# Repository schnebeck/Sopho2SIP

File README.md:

# ErgoLine D340 – Protokoll der PC-Schnittstelle

Offene Dokumentation des seriellen Protokolls, mit dem ein PC ein Philips-Systemtelefon **ErgoLine D340**
(Anlage **Sopho iS3000**, Telekom-Variante Octophon 340) steuert: Anrufe erkennen – mit Anrufernummer –,
annehmen, wählen und auslösen. Ziel: Jede und jeder soll damit einen eigenen TAPI- oder SIP-Daemon bauen können.

**➜ Spezifikation lesen: [schnebeck.github.io/Sopho2SIP/protokoll.html](https://schnebeck.github.io/Sopho2SIP/protokoll.html)**
(im Repository: [`docs/protokoll.html`](docs/protokoll.html))

Die Spezifikation enthält Rahmenformat, alle Meldungen und Aufträge, Zeitverhalten, Ablauf- und Zustandsdiagramme,
die Zuordnung zu SIP und einen Leitfaden für den Daemon. Jede Angabe ist gekennzeichnet als
**bestätigt** (am Gerät gemessen), **Treiber** (aus dem Philips-Treiber abgeleitet) oder **vermutet**.

## Kurzfassung

| | |
|---|---|
| Anschluss | 9-polige Buchse hinten am Telefon, 1:1-Kabel, Pin 2/3/5 |
| Freischaltung | am Telefon: Merkmale → Optionen → „TAPI: Sprache über Telefon“ = Ein |
| Leitung | 1200 Baud, 8O1 |
| Rahmen | `Klasse · Länge · Nutzdaten` – ohne Prüfsumme, ohne Start-/Endzeichen |
| Klassen | `01` Auftrag PC · `02` Meldung Telefon · `03` REJ · `04` ACK · `05` ERR |
| Meldungen | `30` RINGING (mit Anrufernummer) · `31` CONNECTED · `32` DISCONNECTED · `36` DIALTONE · `39` RELEASED · `3e` PROCEEDING · … |
| Aufträge | Anmelden `01 02 01 00` · Wählen `01 L 19 00 98 70 …` · Annehmen `01 02 14 00` · Auflegen `01 02 13 00` |

## Stand

- Empfangsrichtung vollständig mitgeschnitten und entschlüsselt (Anruf mit Nummer, Wahl, Verbindung, Auslösung).
- Senderichtung aus dem originalen Philips-Treiber abgeleitet; der erste Test am Gerät steht aus
  ([`docs/testplan.md`](docs/testplan.md)).
- Offene Fragen stehen am Ende der Spezifikation.

## Weitere Dokumente

| Datei | Inhalt |
|---|---|
| [`docs/protocol.md`](docs/protocol.md) | Arbeitsnotizen zum Protokoll mit Log-Verweisen |
| [`docs/audio_verkabelung.html`](https://schnebeck.github.io/Sopho2SIP/audio_verkabelung.html) | Schaltplan: Audio-Buchse über 600-Ω-Übertrager an die USB-Soundkarte (vorläufig) |
| [`docs/hardware.md`](docs/hardware.md) | Pinbelegung, Messwerte, Menüpunkte, Wartungsmodus des Telefons |
| [`docs/sackgassen.md`](docs/sackgassen.md) | Irrwege, z. B. der inkompatible Octophon-Treiber mit AT-Befehlen |
| [`docs/testplan.md`](docs/testplan.md) | nächste Tests am Gerät |
| [`logs/INDEX.md`](logs/INDEX.md) | Mitschnitte, die die Angaben belegen (Rufnummern durch Platzhalter ersetzt) |
| [`ref/ergoline_tsp/QUELLE.md`](ref/ergoline_tsp/QUELLE.md) | Herkunft des Philips-Treibers (Wayback Machine) mit Prüfsummen |

## Referenzimplementierung (experimentell)

Python 3 mit `pyserial`, keine weiteren Abhängigkeiten:

- `gateway/ergoline/protocol.py` – Rahmen, Meldungen, Aufträge (ohne Ein-/Ausgabe)
- `gateway/ergoline/link.py` – serielle Verbindung mit Quittung und Sitzungslog
- `gateway/ergoline/zustand.py` – Zustandsautomat nach dem Vorbild des Philips-Treibers
- `gateway/sopho2sipd.py` – Daemon: Verbindung, Anmeldung, Keepalive, Anrufdatensätze als JSON-Datei/Webhook ([`docs/anrufdaten.md`](docs/anrufdaten.md))
- `tools/ergo.py` – Mitschnitte dekodieren, mitlesen, Aufträge senden
- Tests: `python3 -m unittest discover -s gateway/tests -v`

```
tools/ergo.py decode logs/serial_20260930_163534.log
gateway/sopho2sipd.py --wiedergabe logs/serial_20260930_163534.log --anrufe -
```

Die Spezifikation wird mit `tools/build_protokoll_doc.py` aus `docs/protokoll.tpl.html` erzeugt.

## Nicht enthalten: der Philips-Treiber

Der Philips-Treiber (`Ergoline.tsp`), Handbuch-Auszüge und das Benutzerhandbuch sind urheberrechtlich geschützt
und liegen nicht im Repository. Der Treiber ist in der Wayback Machine archiviert:

- Direkt-Download: [ergoline.zip (Wayback Machine, 2010-12-01)](https://web.archive.org/web/20101201193039id_/http://tapicall.de/tapi-treiber/nec_philips/telefone/ergoline-serie/ergoline_d330/ergoline.zip)
- SHA-256 `ergoline.zip`: `d278ae82b84d656354e80f650fbd9ae9816d62526e92ea5dcb5483e05b374daf`
- SHA-256 `Ergoline.tsp` (im ZIP): `2b5b2b3e2e3ff51a2ca666b7bc874e9e9d81551a3f67c5357ea8ea297f50b282`

Weitere Fundstellen: [`ref/ergoline_tsp/QUELLE.md`](ref/ergoline_tsp/QUELLE.md) und Abschnitt Quellen der Spezifikation.

## Lizenz

Der Code (`gateway/`, `tools/`) steht unter der **GNU General Public License v3.0 oder später**
(`GPL-3.0-or-later`, siehe [`LICENSE`](LICENSE)). Für die Dokumentation gilt keine gesonderte Lizenz.

## Vorsicht

Eine Telefonanlage lässt sich nicht beliebig zurücksetzen. Nur dokumentierte Aufträge senden, nichts raten, und am
Telefon weder das Service-Menü noch die Wartungscodes 31–34 benutzen.

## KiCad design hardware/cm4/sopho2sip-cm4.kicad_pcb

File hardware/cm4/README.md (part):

# Sopho2SIP-Träger für Compute Module 4 (Entwurf 0.3)

Trägerplatine für das Raspberry Pi **Compute Module 4** als Gerät zum Einstecken: alle Kabel hinten, kurze Wege zur
D340, vorne µSD, Status-LEDs und drei Taster (Annehmen, Konfiguration, Ein/Aus); Lüfter temperaturgesteuert;
Gehäuse aus dem 3D-Drucker.

- **Speicher:** CM4 mit **eMMC** *oder* **CM4 Lite** mit **µSD-Karte**. Der Sockel ist immer bestückt. Beim
  eMMC-Modul sind die SD-Pins im Modul offen, der Sockel bleibt dann ungenutzt.
- **Netz:** **WLAN** über das CM4 mit Funk (Antenne auf dem Modul, zur linken Platinenkante; oder U.FL)
  *oder/und* **Ethernet 10/100** (RJ45 mit Übertrager). Der Betrieb wird per Software gewählt.
- **D340:** isolierte RS-232 (ADuM5211 + MAX3232, **4P4C-Buchse**) und Sprechweg über zwei Übertrager (RJ12).
  Zur D340 führt ein Adapterkabel 4P4C → DE9-Stecker (4P4C 1 → 5 GND, 2 → 2 RxD, 3 → 3 TxD).

| Datei | Inhalt |
|---|---|
| `erzeuge_schaltplan.py` | hierarchischer Schaltplan: `SOLL_*` (Verbindungen je Blatt), `blatt_*()` (Zeichnung), `main()` (Wurzelblatt) |
| `erzeuge_layout.py` | Leiterplatte aus der KiCad-Netzliste: Platzierung, Lagen, Flächen, Sperrzonen, Regeln, Routing, DRC, Fertigungsdaten |
| `erzeuge_bestellliste.py` | `stueckliste_digikey.csv` mit Herstellernummern und Digikey-Bestand |
| `sopho2sip-cm4.kicad_sch`, `*.kicad_sch` | Wurzelblatt und Kindblätter (erzeugt) |
| `sopho2sip-cm4.kicad_pcb`, `.kicad_dru` | Leiterplatte und JLCPCB-Regeln (erzeugt) |
| `sopho2sip.kicad_sym`, `sym-lib-table`, `fp-lib-table` | Projektbibliotheken; eigene Footprints in `hardware/bibliothek/` |
| `sopho2sip-cm4.pdf` | alle 9 Schaltplanblätter |
| `netzliste.txt`, `stueckliste.csv` | Soll-Netzliste, KiCad-Stückliste |
| `handlage/`, `.generiert.json` | von Hand nachgebesserte Blätter; Fingerabdrücke der zuletzt erzeugten Zeichnung |

Neu erzeugen und prüfen:
```
hardware/bibliothek/erzeuge_footprints.py         # eigene Footprints (Übertrager, RJ12, DF40 mit Pins 101–200)
hardware/cm4/erzeuge_schaltplan.py --pruefen      # ERC + Abgleich der Netzliste mit SOLL
hardware/cm4/erzeuge_layout.py --routen --pruefen # Platine, FreeRouting, DRC
hardware/cm4/erzeuge_layout.py --nur-fertigung    # Gerber/Bohrdaten/Bestückung/STEP/Bild nach fertigung/
hardware/cm4/erzeuge_bestellliste.py
```
Die UUIDs sind reproduzierbar: Schaltplan und Platine bleiben beim Neuerzeugen verknüpft („Platine aus Schaltplan
aktualisieren“ in KiCad funktioniert weiter).

**Zeichnung von Hand nachbessern:** Blätter in KiCad schöner setzen (Bauteile, Beschriftungen, Leitungen, Labels
verschieben) und speichern, dann den Generator laufen lassen. Er erkennt die geänderten Blätter am Fingerabdruck der
Zeichnung, prüft die Netzliste gegen SOLL und übernimmt sie nach `handlage/`. Ab dann kommt die Zeichnung dieser
Blätter von dort; Werte, Footprints und Symbole weiter aus SOLL (in KiCad geänderte Werte werden mit Hinweis
zurückgesetzt). Ändert die Handarbeit eine Verbindung, schreibt der Generator nichts und nennt die Abweichung.
```
hardware/cm4/erzeuge_schaltplan.py --pruefen                          # Änderungen im Projektordner übernehmen
hardware/cm4/erzeuge_schaltplan.py --handlage-aus ~/kopie --pruefen    # … aus einer Kopie des Projekts
hardware/cm4/erzeuge_schaltplan.py --handlage-verwerfen Bedienung      # Blatt wieder vom Generator zeichnen lassen
```
Kommt in SOLL ein Bauteil auf einem Blatt mit Handlage hinzu (oder fällt weg), bricht der Generator ab: das Blatt in
KiCad nachziehen oder die Handlage verwerfen.

**Texte** (Hinweiskästen, Texte, Blocktitel) gehören dem Generator. In KiCad geänderte Texte schreibt der Generator
an die Stelle im Quelltext zurück, an der sie entstehen (`p.notiz(…)`, `p.text(…)`, `rahmen_(…)`); ein neuer Absatz
im Kasten wird ein weiteres Argument von `notiz`. Ersetzt wird nur, wenn dort feste Literale genau den bisherigen
Text ergeben; sonst bleibt der Text als Handtext in `.generiert.json` und wird gemeldet. Ändert sich nur Text, nicht
die Lage, entsteht keine Handlage. In KiCad neu angelegte oder gelöschte Texte meldet der Generator nur.
Hinweise stehen in Textkästen (`notiz`): KiCad bricht innerhalb der Kastenbreite um, die Höhe schätzt der Generator.

## Blätter und Bauteile

| Blatt | Bauteile | Warum |
|---|---|---|
| CM4 | J11/J12 **Hirose DF40C-100DS-0.4V(51)** (1,5 mm Stapelhöhe), C40/C41, H5–H8 | Pinbelegung und Lage aus Datenblatt und CM4IO-Referenzlayout; **GPIO_VREF = 3,3 V** |
| | JP10 **nRPIBOOT** | gesteckt: das CM4 startet als USB-Gerät → `rpiboot` über USB-C, eMMC erscheint als Laufwerk |
| | D10 (ACT), Q10 **BSS84** + D11 (PWR) | Aktivitäts-Pin senkt bis 20 mA; PI_LED_nPWR muss laut Datenblatt gepuffert werden |
| Versorgung | J10 **USB-C** GCT USB4105, F1 Polyfuse 2 A, D12 **SMAJ5.0CA**, R10/R11 5,1 kΩ, U10 **USBLC6-2SC6** | eine Buchse für 5 V und USB 2.0 (rpiboot) |
| µSD | J13 Hirose DM3AT, U11 **AP22804AW5**, R14 12 kΩ | Lastschalter für die Kartenspannung wie Datenblatt (dort RT9742) |
| Ethernet | J14 **Würth 7499010211A** (RJ45 mit Übertrager, LEDs), U12 **TPD4E05U06**, C45, R15/R16 | Mittelanzapfungen über 100 nF an GND, ESD an den Paaren, LEDs low-aktiv |
| Audio-Codec | U2 **TI TLV320AIC3204** (VQFN-32), U6 Oszillator 12 MHz, U4 AP2112K-3.3 | **WM8731 ist abgekündigt**, SGTL5000/WM8960 ebenso bzw. nicht lieferbar. Der AIC3204 hat einen Linux-Treiber (`tlv320aic32x4`); Vorlage für das Overlay ist `audiosense-pi` (I²C 0x18, MCLK 12 MHz, Reset an GPIO26). **I²C an GPIO0/1 (I2C0)**, weil GPIO3 der Ein/Aus-Taster ist. LOL treibt den 600-Ω-Übertrager (Last ≥ 600 Ω laut Datenblatt) |
| Sprechweg | T1/T2 **Bourns SM-LP-5001** (600:600, 2 kV), J2 **Würth 615006138421** (RJ12/6P6C) | Amphenol 54601 ist abgekündigt |
| RS-232 | U3 **ADuM5211**, U5 **MAX3232E**, J3 **Würth 615004143821** (4P4C liegend) | statt DE9 (31 mm Kante, 13 mm hoch): verriegelnd, klein, nicht mit RJ12/RJ45 verwechselbar |
| CM4 selbst | M1 Platzhalter | steht in der Stückliste, wird gesteckt (nicht in den Bestückungsdaten); 3D-Modell 1,5 mm über J11/J12 |
| Bedienung | SW1 Annehmen/Auflegen (GPIO25), **SW2 Konfiguration (GPIO27)**, **SW3 Ein/Aus (GPIO3)**, D1–D3 (GPIO23/24/22) | D3 + SW2 für Einstellungen am Gerät; alle LEDs vorne für Lichtleiter |
| | SW3, R9 (unbestückt) | **Ein/Aus mit einem Taster:** im Betrieb fährt `gpio-shutdown` sauber herunter; im Halt weckt der Bootloader das CM4 über GPIO3 (`WAKE_ON_GPIO=1`, Werkseinstellung). GLOBAL_EN bleibt unbenutzt (Datenblatt: nur nach dem Herunterfahren auf Low ziehen) |
| Lüfter | Q11 **AO3400A**, D13 **MBR140SFT1G**, R17/R18, C46, J15 **JST PH 2-polig** | 5-V-Lüfter, Low-Side-Schalter an GPIO12 (PWM-fähig); die SoC-Temperatur des CM4 steuert über `gpio-fan` |

Die vollständige Bestellliste mit Digikey-Nummern und dem am 2026-10-03 geprüften Bestand steht in
`stueckliste_digikey.csv`. Keramikkondensatoren und Widerstände sind Standardteile; deren Bestand schwankt, der
Digikey-BOM-Manager schlägt gleichwertige Teile vor.

## Leiterplatte

- **Maße:** 110 × 85 mm, 4 Lagen, 1,6 mm, JLCPCB-Aufbau **JLC04161H-7628** (bei der Bestellung „Impedance Control“
  mit diesem Aufbau wählen).
- **Lagen:** F.Cu Signale · **In1 GND** · **In2 +3V3** · B.Cu Signale. Außenlagen nach dem Routing mit Masse gefüllt.
- **Impedanz** (berechnet, mit dem JLC-Rechner gegenprüfen): Ethernet 100 Ω differenziell = 0,20 mm / 0,17 mm,
  USB 90 Ω = 0,22 mm / 0,13 mm (Mikrostreifen über 0,21 mm Prepreg).
- **Anordnung:** hinten USB-C, RJ45, DE9, RJ12; CM4 links mit der Antenne zur linken Kante (kupferfreie Zone
  9,5 × 15 mm auf allen Lagen, Datenblatt: mind. 8 × 15 mm); vorne µSD, LEDs, Taster.
- **Isolation:** GND_ISO (RS-232) und GNDA (Sprechweg) sind eigene Bereiche mit eigenen Flächen auf allen Lagen.
  1 mm breite kupferfreie Trennstreifen auf allen Lagen; nur der ADuM5211 und die Übertrager überbrücken sie.
- **Regeln:** JLCPCB-Standard (Bahn/Abstand ≥ 0,09 mm, Bohrung ≥ 0,15 mm, Kupfer zur Kante ≥ 0,3 mm), in
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
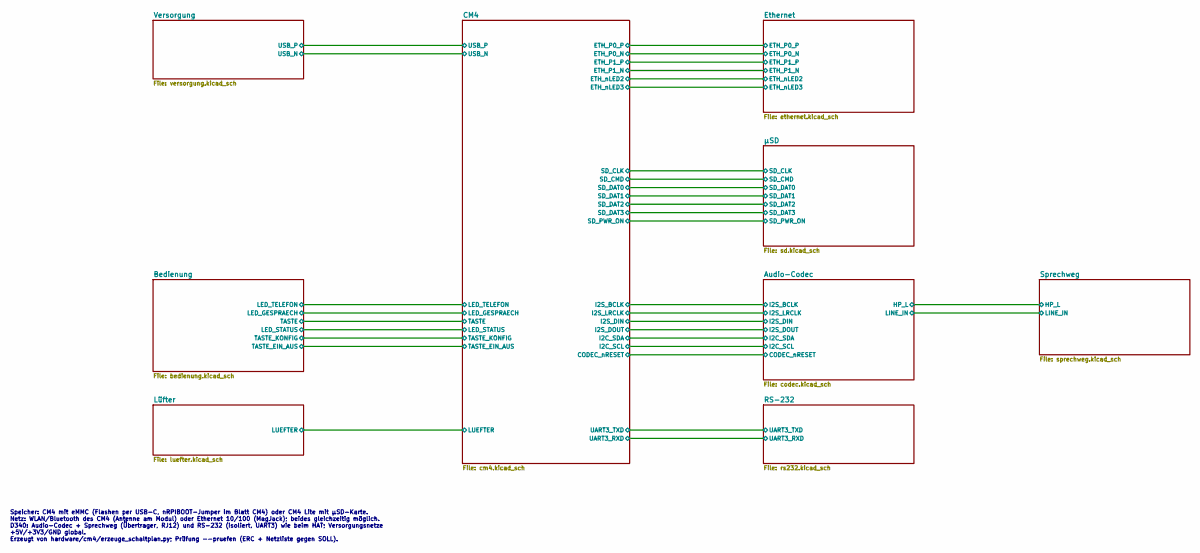
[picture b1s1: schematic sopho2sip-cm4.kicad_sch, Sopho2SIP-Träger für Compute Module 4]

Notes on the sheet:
Speicher: CM4 mit eMMC (Flashen per USB-C, nRPIBOOT-Jumper im Blatt CM4) oder CM4 Lite mit µSD-Karte. Netz: WLAN/Bluetooth des CM4 (Antenne am Modul) oder Ethernet 10/100 (MagJack); beides gleichzeitig möglich. D340: Audio-Codec + Sprechweg (Übertrager, RJ12) und RS-232 (isoliert, UART3) wie beim H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

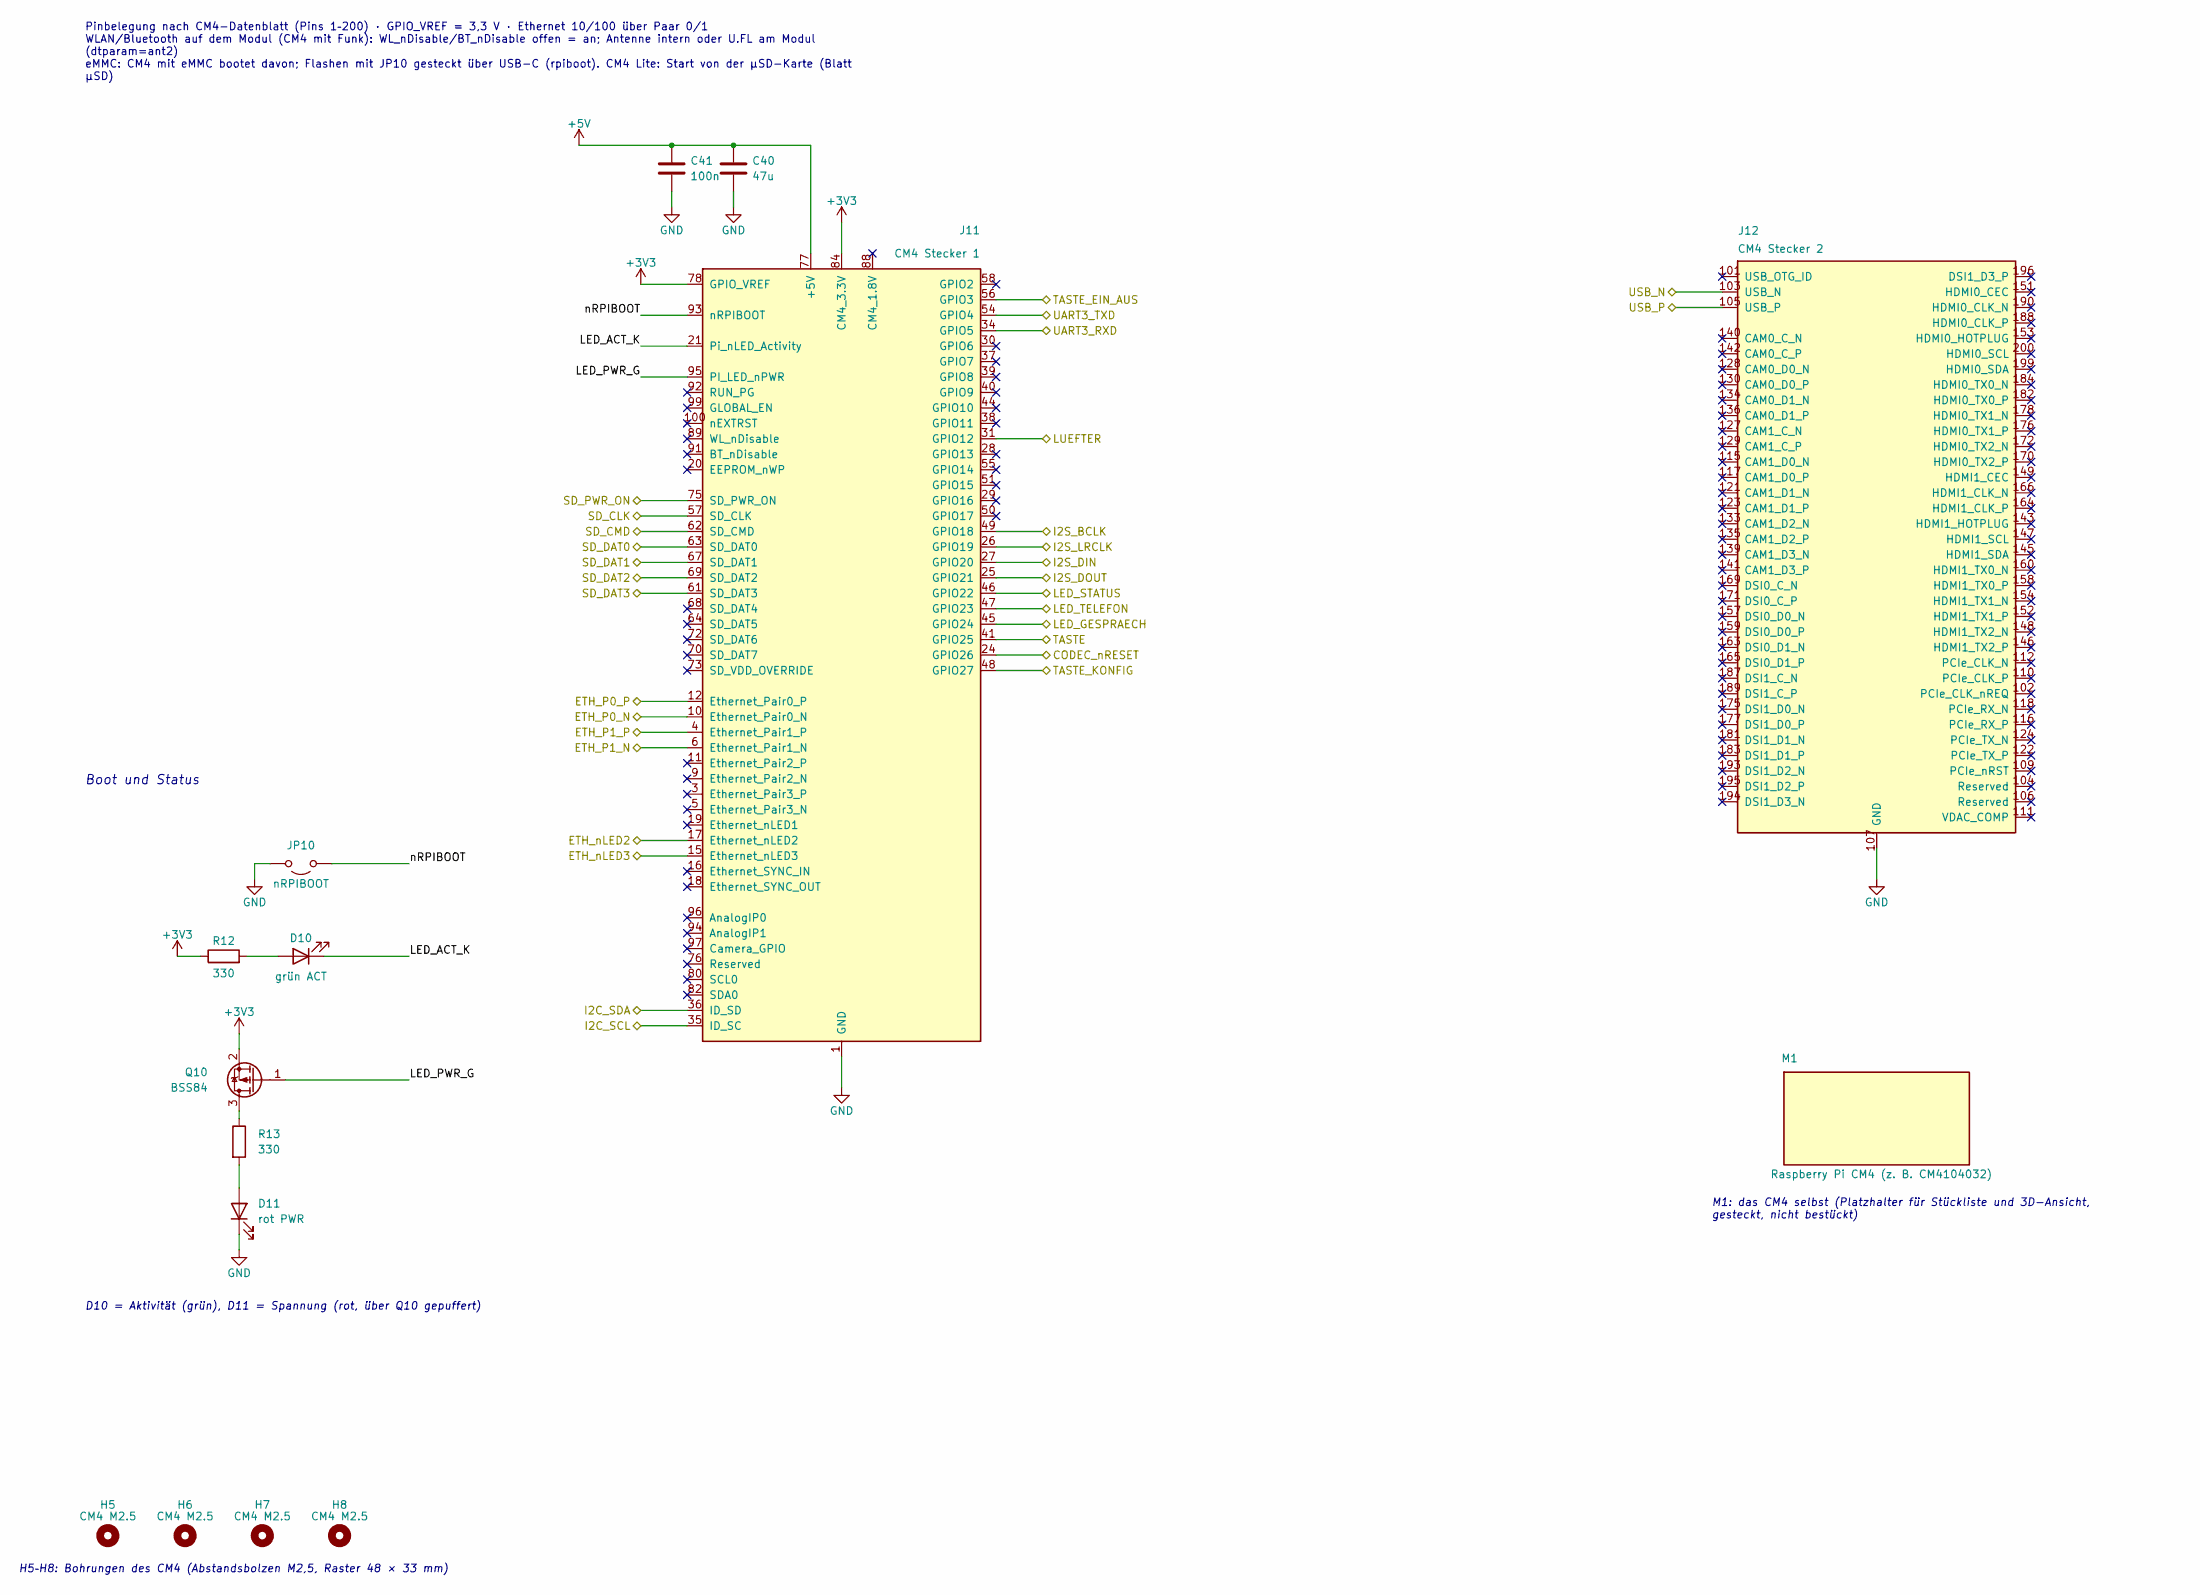
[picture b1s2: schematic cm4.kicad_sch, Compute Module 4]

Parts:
C40: 47u; C_1206_3216Metric
C41: 100n; C_0603_1608Metric
D10: grün ACT; LED_0603_1608Metric
D11: rot PWR; LED_0603_1608Metric
H5, H6, H7, H8: CM4 M2.5; MountingHole_2.7mm_M2.5
J11: CM4 Stecker 1; Hirose_DF40C-100DS-0.4V_2x50_P0.4mm
J12: CM4 Stecker 2; Hirose_DF40C-100DS-0.4V_2x50_P0.4mm_Pins101-200
JP10: nRPIBOOT; PinHeader_1x02_P2.54mm_Vertical
M1: Raspberry Pi CM4 (z. B. CM4104032); CM4_Modul_Platzhalter
Q10: BSS84; SOT-23
R12, R13: 330; R_0603_1608Metric

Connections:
+3V3: J11.78 (GPIO_VREF), J11.84 (CM4_3.3V), J11.86 (CM4_3.3V), Q10.2 (S), R12.1; also elsewhere on the board
+5V: C40.1, C41.1, J11.77 (+5V), J11.79 (+5V), J11.81 (+5V), J11.83 (+5V), J11.85 (+5V), J11.87 (+5V); also elsewhere on the board
/Audio-Codec/CODEC_nRESET: J11.24 (GPIO26); also elsewhere on the board
/Audio-Codec/I2C_SCL: J11.35 (ID_SC); also elsewhere on the board
/Audio-Codec/I2C_SDA: J11.36 (ID_SD); also elsewhere on the board
/Audio-Codec/I2S_BCLK: J11.49 (GPIO18); also elsewhere on the board
/Audio-Codec/I2S_DIN: J11.27 (GPIO20); also elsewhere on the board
/Audio-Codec/I2S_DOUT: J11.25 (GPIO21); also elsewhere on the board
/Audio-Codec/I2S_LRCLK: J11.26 (GPIO19); also elsewhere on the board
/Bedienung/LED_GESPRAECH: J11.45 (GPIO24); also elsewhere on the board
/Bedienung/LED_STATUS: J11.46 (GPIO22); also elsewhere on the board
/Bedienung/LED_TELEFON: J11.47 (GPIO23); also elsewhere on the board
/Bedienung/TASTE: J11.41 (GPIO25); also elsewhere on the board
/Bedienung/TASTE_EIN_AUS: J11.56 (GPIO3); also elsewhere on the board
/Bedienung/TASTE_KONFIG: J11.48 (GPIO27); also elsewhere on the board
/CM4/ETH_P0_N: J11.10 (Ethernet_Pair0_N); also elsewhere on the board
/CM4/ETH_P0_P: J11.12 (Ethernet_Pair0_P); also elsewhere on the board
/CM4/ETH_P1_N: J11.6 (Ethernet_Pair1_N); also elsewhere on the board
/CM4/ETH_P1_P: J11.4 (Ethernet_Pair1_P); also elsewhere on the board
/CM4/ETH_nLED2: J11.17 (Ethernet_nLED2); also elsewhere on the board
/CM4/ETH_nLED3: J11.15 (Ethernet_nLED3); also elsewhere on the board
/CM4/LED_ACT_K: D10.1 (K), J11.21 (Pi_nLED_Activity)
/CM4/LED_PWR_G: J11.95 (PI_LED_nPWR), Q10.1 (G)
/CM4/LUEFTER: J11.31 (GPIO12); also elsewhere on the board
/CM4/SD_CLK: J11.57 (SD_CLK); also elsewhere on the board
/CM4/SD_CMD: J11.62 (SD_CMD); also elsewhere on the board
/CM4/SD_DAT0: J11.63 (SD_DAT0); also elsewhere on the board
/CM4/SD_DAT1: J11.67 (SD_DAT1); also elsewhere on the board
/CM4/SD_DAT2: J11.69 (SD_DAT2); also elsewhere on the board
/CM4/SD_DAT3: J11.61 (SD_DAT3); also elsewhere on the board
/CM4/SD_PWR_ON: J11.75 (SD_PWR_ON); also elsewhere on the board
/CM4/UART3_RXD: J11.34 (GPIO5); also elsewhere on the board
/CM4/UART3_TXD: J11.54 (GPIO4); also elsewhere on the board
/CM4/USB_N: J12.103 (USB_N); also elsewhere on the board
/CM4/USB_P: J12.105 (USB_P); also elsewhere on the board
/CM4/nRPIBOOT: J11.93 (nRPIBOOT), JP10.1 (A)
GND: C40.2, C41.2, D11.1 (K), J11.1 (GND), J11.2 (GND), J11.7 (GND), J11.8 (GND), J11.13 (GND), J11.14 (GND), J11.22 (GND), J11.23 (GND), J11.32 (GND), J11.33 (GND), J11.42 (GND), J11.43 (GND), J11.52 (GND), J11.53 (GND), J11.59 (GND), J11.60 (GND), J11.65 (GND), J11.66 (GND), J11.71 (GND), J11.74 (GND), J11.98 (GND), J12.107 (GND), J12.108 (GND), J12.113 (GND), J12.114 (GND), J12.119 (GND), J12.120 (GND), J12.125 (GND), J12.126 (GND), J12.131 (GND), J12.132 (GND), J12.137 (GND), J12.138 (GND), J12.144 (GND), J12.150 (GND), J12.155 (GND), J12.156 (GND), J12.161 (GND), J12.162 (GND), J12.167 (GND), J12.168 (GND), J12.173 (GND), J12.174 (GND), J12.179 (GND), J12.180 (GND), J12.185 (GND), J12.186 (GND), J12.191 (GND), J12.192 (GND), J12.197 (GND), J12.198 (GND), JP10.2 (B); also elsewhere on the board
unnamed: D10.2 (A), R12.2
unnamed: D11.2 (A), R13.2
unnamed: Q10.3 (D), R13.1

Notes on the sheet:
Boot und Status
D10 = Aktivität (grün), D11 = Spannung (rot, über Q10 gepuffert)
H5–H8: Bohrungen des CM4 (Abstandsbolzen M2,5, Raster 48 × 33 mm)
M1: das CM4 selbst (Platzhalter für Stückliste und 3D-Ansicht, gesteckt, nicht bestückt)
Pinbelegung nach CM4-Datenblatt (Pins 1–200) · GPIO_VREF = 3,3 V · Ethernet 10/100 über Paar 0/1 WLAN/Bluetooth auf dem Modul (CM4 mit Funk): WL_nDisable/BT_nDisable offen = an; Antenne intern oder U.FL am Modul (dtparam=ant2) eMMC: CM4 mit eMMC bootet davon; Flashen mit JP10 gesteckt über USB-C (r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

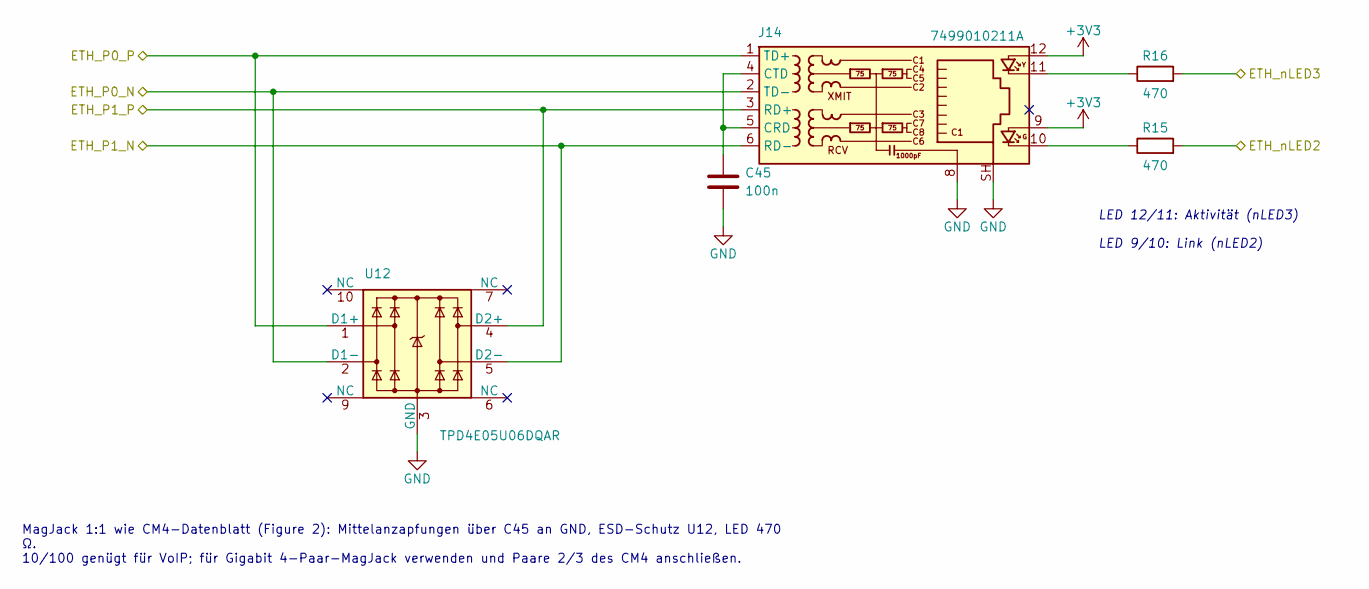
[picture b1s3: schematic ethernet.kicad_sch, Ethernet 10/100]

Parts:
C45: 100n; C_0603_1608Metric
J14: 7499010211A; RJ45_Wuerth_7499010211A_Horizontal
R15, R16: 470; R_0603_1608Metric
U12: TPD4E05U06DQAR; USON-10_2.5x1.0mm_P0.5mm

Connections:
+3V3: J14.9, J14.12; also elsewhere on the board
/CM4/ETH_P0_N: J14.2 (TD-), U12.2 (D1-); also elsewhere on the board
/CM4/ETH_P0_P: J14.1 (TD+), U12.1 (D1+); also elsewhere on the board
/CM4/ETH_P1_N: J14.6 (RD-), U12.5 (D2-); also elsewhere on the board
/CM4/ETH_P1_P: J14.3 (RD+), U12.4 (D2+); also elsewhere on the board
/CM4/ETH_nLED2: R15.2; also elsewhere on the board
/CM4/ETH_nLED3: R16.2; also elsewhere on the board
GND: C45.2, J14.8, J14.SH, U12.3 (GND), U12.8 (GND); also elsewhere on the board
unnamed: C45.1, J14.4 (CTD), J14.5 (CRD)
unnamed: J14.10, R15.1
unnamed: J14.11, R16.1

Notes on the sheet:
LED 12/11: Aktivität (nLED3)
LED 9/10: Link (nLED2)
MagJack 1:1 wie CM4-Datenblatt (Figure 2): Mittelanzapfungen über C45 an GND, ESD-Schutz U12, LED 470 Ω. 10/100 genügt für VoIP; für Gigabit 4-Paar-MagJack verwenden und Paare 2/3 des CM4 anschließen.

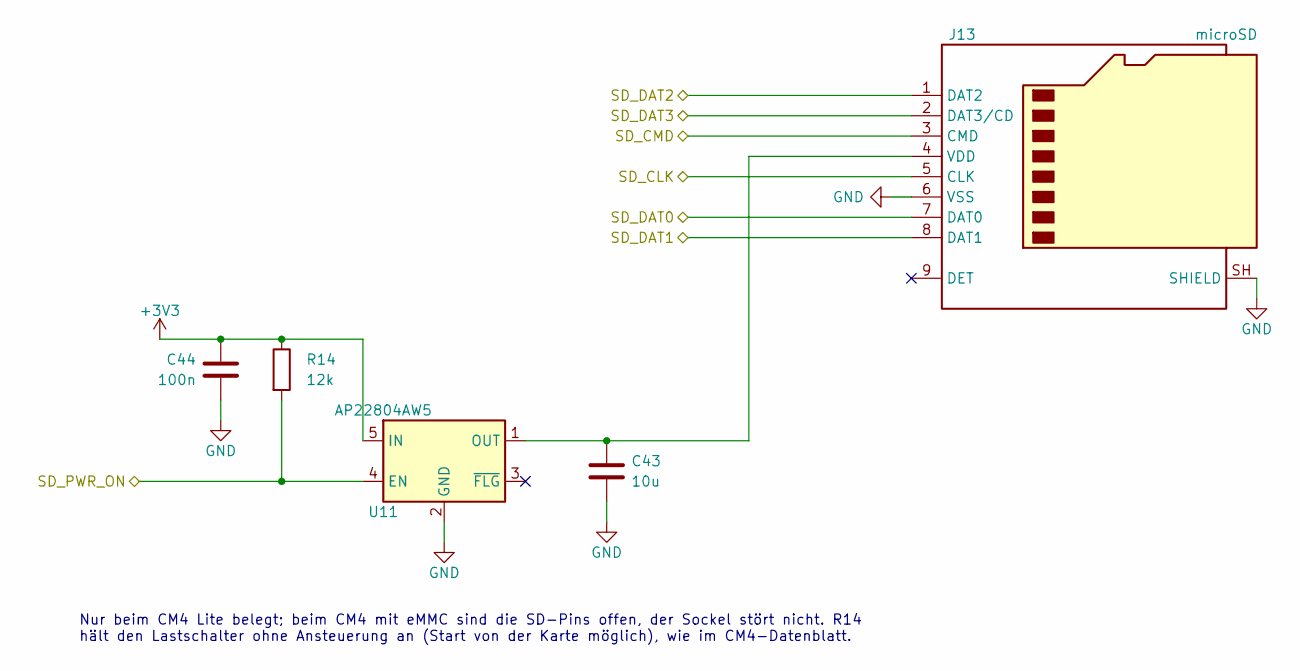
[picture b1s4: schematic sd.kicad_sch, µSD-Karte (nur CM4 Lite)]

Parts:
C43: 10u; C_0805_2012Metric
C44: 100n; C_0603_1608Metric
J13: microSD; microSD_HC_Hirose_DM3AT-SF-PEJM5
R14: 12k; R_0603_1608Metric
U11: AP22804AW5; SOT-23-5

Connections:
+3V3: C44.1, R14.1, U11.5 (IN); also elsewhere on the board
/CM4/SD_CLK: J13.5 (CLK); also elsewhere on the board
/CM4/SD_CMD: J13.3 (CMD); also elsewhere on the board
/CM4/SD_DAT0: J13.7 (DAT0); also elsewhere on the board
/CM4/SD_DAT1: J13.8 (DAT1); also elsewhere on the board
/CM4/SD_DAT2: J13.1 (DAT2); also elsewhere on the board
/CM4/SD_DAT3: J13.2 (DAT3/CD); also elsewhere on the board
/CM4/SD_PWR_ON: R14.2, U11.4 (EN); also elsewhere on the board
GND: C43.2, C44.2, J13.6 (VSS), J13.SH (SHIELD), U11.2 (GND); also elsewhere on the board
unnamed: C43.1, J13.4 (VDD), U11.1 (OUT)

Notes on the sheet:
Nur beim CM4 Lite belegt; beim CM4 mit eMMC sind die SD-Pins offen, der Sockel stört nicht. R14 hält den Lastschalter ohne Ansteuerung an (Start von der Karte möglich), wie im CM4-Datenblatt.

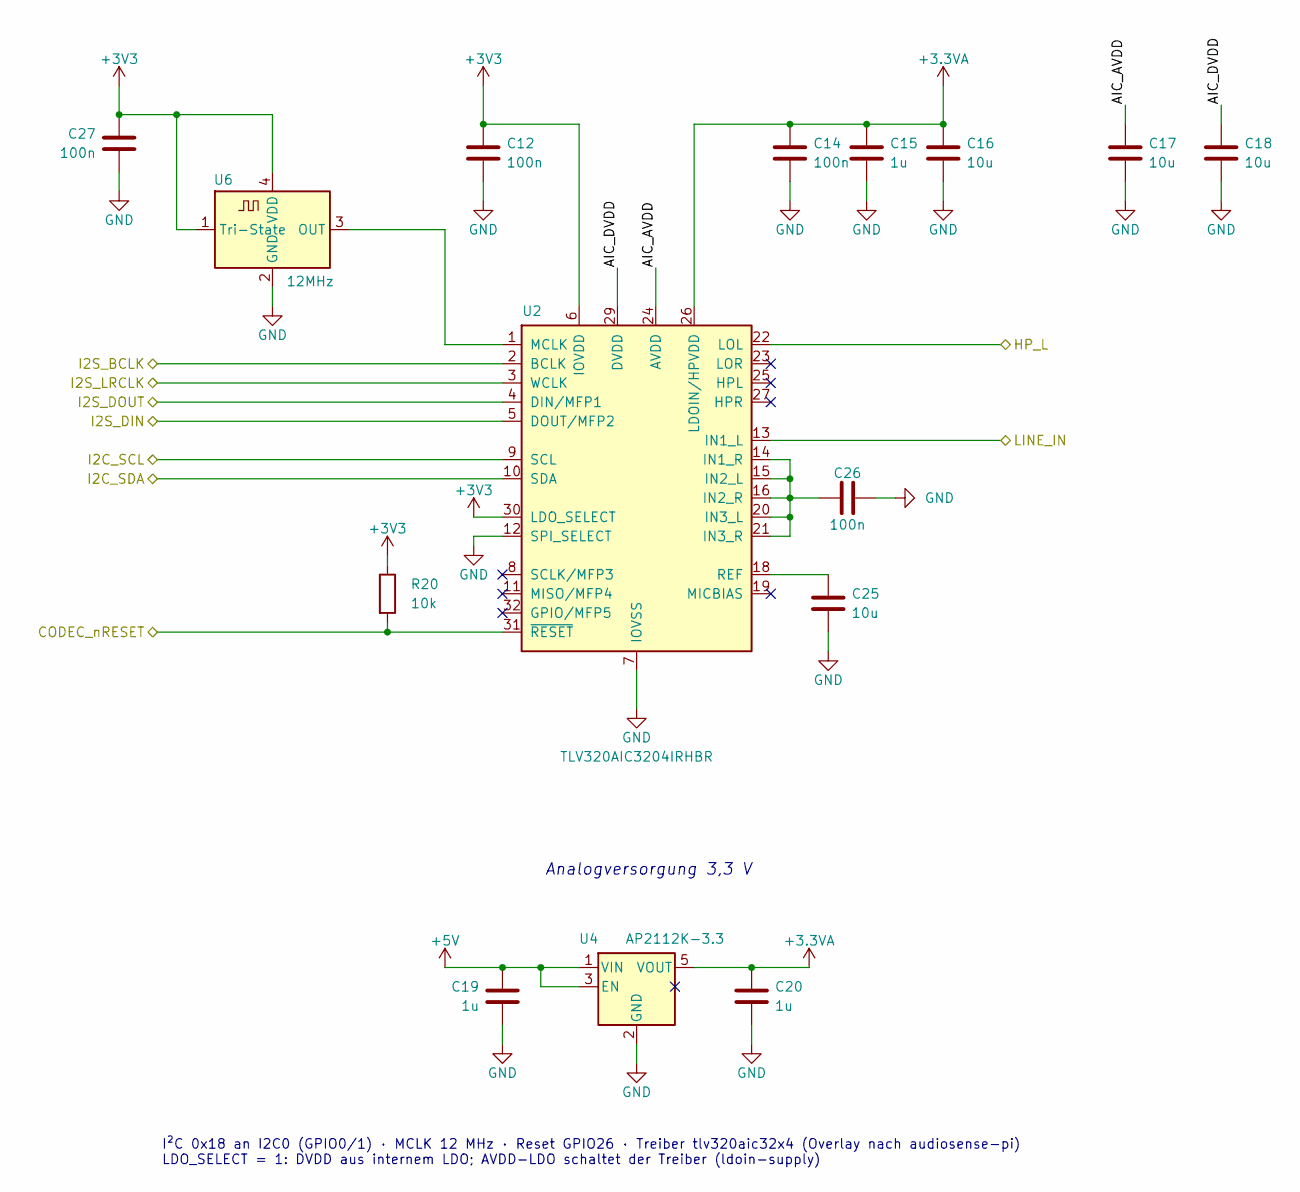
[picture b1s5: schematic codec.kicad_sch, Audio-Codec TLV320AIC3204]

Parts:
C12, C14, C26, C27: 100n; C_0603_1608Metric
C15, C19, C20: 1u; C_0603_1608Metric
C16, C17, C18, C25: 10u; C_0805_2012Metric
R20: 10k; R_0603_1608Metric
U2: TLV320AIC3204IRHBR; Texas_RHB0032E_VQFN-32-1EP_5x5mm_P0.5mm_EP3.45x3.45mm_Therm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
U4: AP2112K-3.3; SOT-23-5
U6: 12MHz; Oscillator_SMD_ECS_2520MV-xxx-xx-4Pin_2.5x2.0mm

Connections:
+3.3VA: C14.1, C15.1, C16.1, C20.1, U2.26 (LDOIN/HPVDD), U4.5 (VOUT)
+3V3: C12.1, C27.1, R20.1, U2.6 (IOVDD), U2.30 (LDO_SELECT), U6.1 (Tri-State), U6.4 (VDD); also elsewhere on the board
+5V: C19.1, U4.1 (VIN), U4.3 (EN); also elsewhere on the board
/Audio-Codec/AIC_AVDD: C17.1, U2.24 (AVDD)
/Audio-Codec/AIC_DVDD: C18.1, U2.29 (DVDD)
/Audio-Codec/CODEC_nRESET: R20.2, U2.31 (~RESET); also elsewhere on the board
/Audio-Codec/HP_L: U2.22 (LOL); also elsewhere on the board
/Audio-Codec/I2C_SCL: U2.9 (SCL); also elsewhere on the board
/Audio-Codec/I2C_SDA: U2.10 (SDA); also elsewhere on the board
/Audio-Codec/I2S_BCLK: U2.2 (BCLK); also elsewhere on the board
/Audio-Codec/I2S_DIN: U2.5 (DOUT/MFP2); also elsewhere on the board
/Audio-Codec/I2S_DOUT: U2.4 (DIN/MFP1); also elsewhere on the board
/Audio-Codec/I2S_LRCLK: U2.3 (WCLK); also elsewhere on the board
/Audio-Codec/LINE_IN: U2.13 (IN1_L); also elsewhere on the board
GND: C12.2, C14.2, C15.2, C16.2, C17.2, C18.2, C19.2, C20.2, C25.2, C26.2, C27.2, U2.7 (IOVSS), U2.12 (SPI_SELECT), U2.17 (AVSS), U2.28 (DVSS), U2.33 (EP), U4.2 (GND), U6.2 (GND); also elsewhere on the board
unnamed: C26.1, U2.14 (IN1_R), U2.15 (IN2_L), U2.16 (IN2_R), U2.20 (IN3_L), U2.21 (IN3_R)
unnamed: U2.1 (MCLK), U6.3 (OUT)
unnamed: C25.1, U2.18 (REF)

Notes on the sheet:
Analogversorgung 3,3 V
I²C 0x18 an I2C0 (GPIO0/1) · MCLK 12 MHz · Reset GPIO26 · Treiber tlv320aic32x4 (Overlay nach audiosense-pi) LDO_SELECT = 1: DVDD aus internem LDO; AVDD-LDO schaltet der Treiber (ldoin-supply)

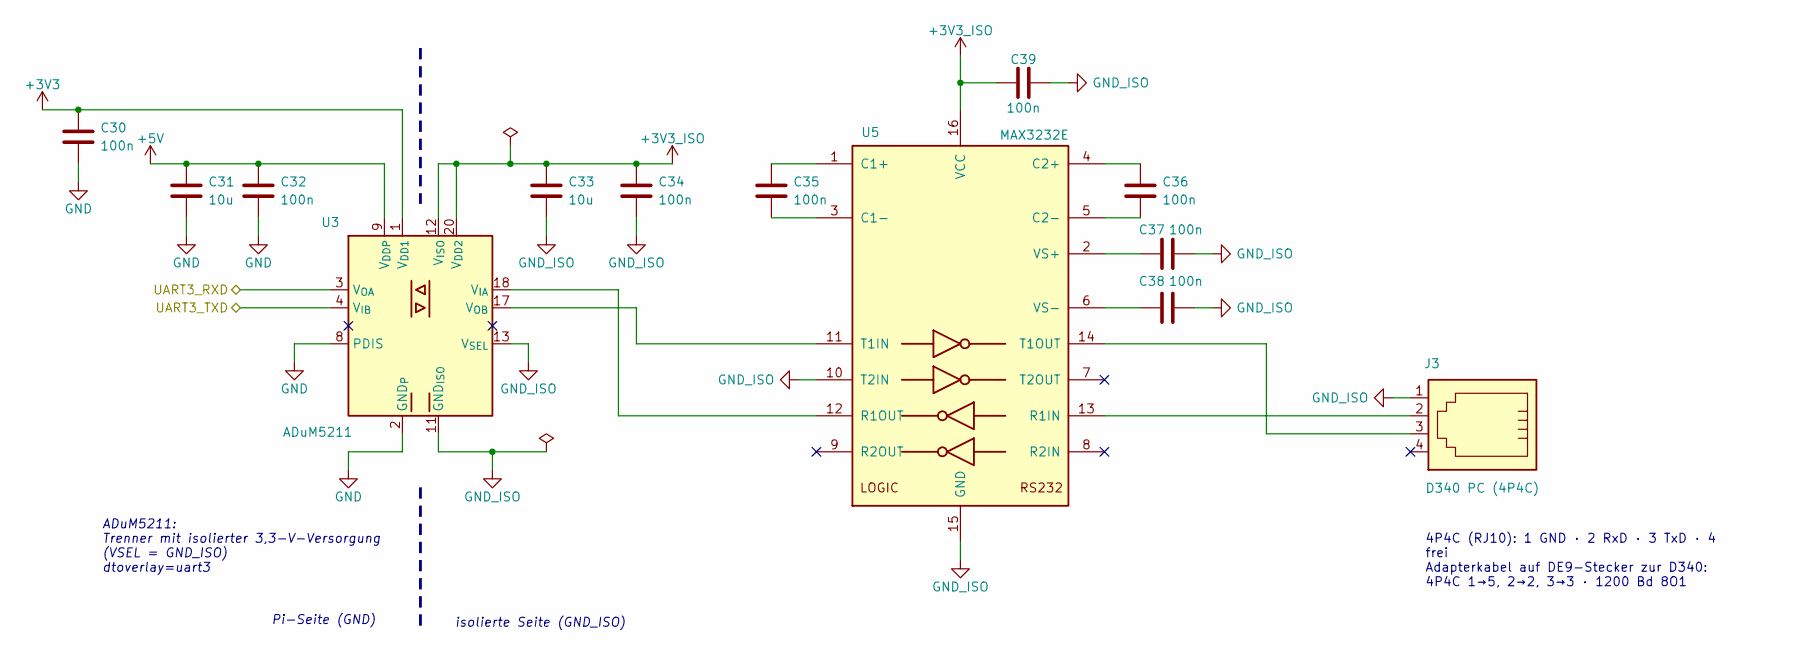
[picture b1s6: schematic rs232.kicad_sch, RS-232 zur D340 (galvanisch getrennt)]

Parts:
C30, C32, C34, C35, C36, C37, C38, C39: 100n; C_0603_1608Metric
C31, C33: 10u; C_0805_2012Metric
J3: D340 PC (4P4C); RJ10_Wuerth_615004143821_Horizontal
U3: ADuM5211; SSOP-20_5.3x7.2mm_P0.65mm
U5: MAX3232E; SOIC-16_3.9x9.9mm_P1.27mm

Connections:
+3V3: C30.1, U3.1 (V_{DD1}); also elsewhere on the board
+3V3_ISO: C33.1, C34.1, C39.1, U3.12 (V_{ISO}), U3.20 (V_{DD2}), U5.16 (VCC)
+5V: C31.1, C32.1, U3.9 (V_{DDP}); also elsewhere on the board
/CM4/UART3_RXD: U3.3 (V_{OA}); also elsewhere on the board
/CM4/UART3_TXD: U3.4 (V_{IB}); also elsewhere on the board
GND: C30.2, C31.2, C32.2, U3.2 (GND_{P}), U3.5 (GND_{P}), U3.6 (GND_{P}), U3.8 (PDIS), U3.10 (GND_{P}); also elsewhere on the board
GND_ISO: C33.2, C34.2, C37.2, C38.2, C39.2, J3.1, U3.11 (GND_{ISO}), U3.13 (V_{SEL}), U3.15 (GND_{ISO}), U3.16 (GND_{ISO}), U3.19 (GND_{ISO}), U5.10 (T2IN), U5.15 (GND)
unnamed: U3.18 (V_{IA}), U5.12 (R1OUT)
unnamed: U3.17 (V_{OB}), U5.11 (T1IN)
unnamed: C35.1, U5.1 (C1+)
unnamed: C35.2, U5.3 (C1-)
unnamed: C36.1, U5.4 (C2+)
unnamed: C36.2, U5.5 (C2-)
unnamed: J3.2, U5.13 (R1IN)
unnamed: J3.3, U5.14 (T1OUT)
unnamed: C37.1, U5.2 (VS+)
unnamed: C38.1, U5.6 (VS-)

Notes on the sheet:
Pi-Seite (GND)
isolierte Seite (GND_ISO)
ADuM5211: Trenner mit isolierter 3,3-V-Versorgung (VSEL = GND_ISO) dtoverlay=uart3
4P4C (RJ10): 1 GND · 2 RxD · 3 TxD · 4 frei Adapterkabel auf DE9-Stecker zur D340: 4P4C 1→5, 2→2, 3→3 · 1200 Bd 8O1

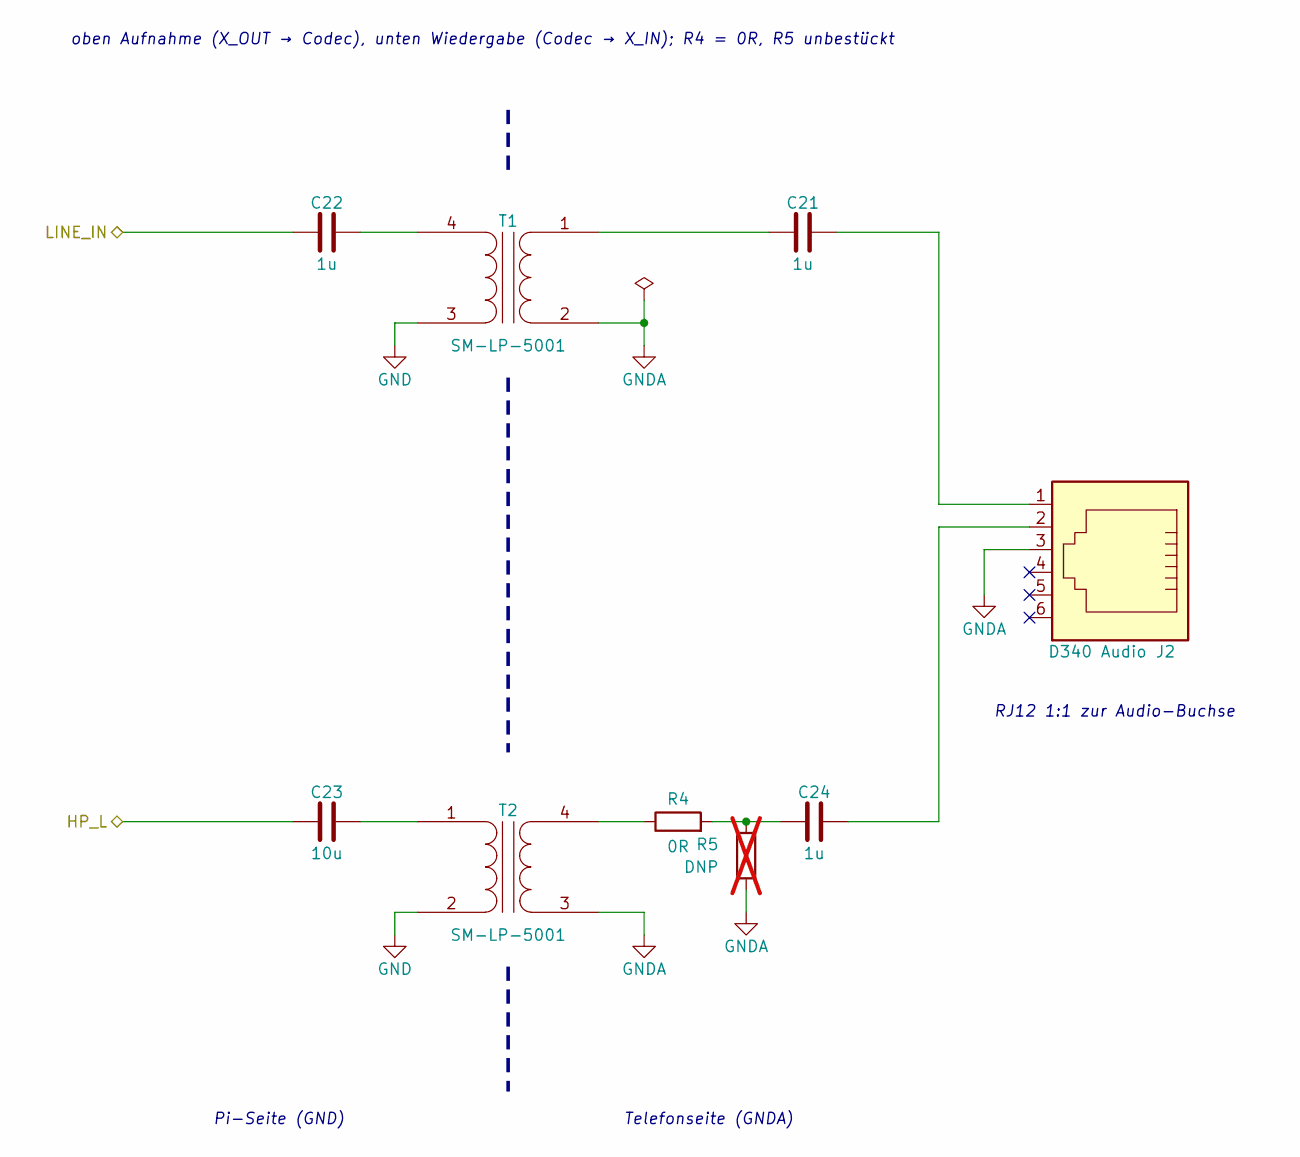
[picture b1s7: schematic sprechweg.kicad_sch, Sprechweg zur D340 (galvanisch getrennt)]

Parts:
C21, C24: 1u; C_0805_2012Metric
C22: 1u; C_0603_1608Metric
C23: 10u; C_0805_2012Metric
J2: D340 Audio; RJ12_Wuerth_615006138421_Horizontal
R4: 0R; R_0603_1608Metric
R5: DNP; R_0603_1608Metric; not fitted
T1, T2: SM-LP-5001; Bourns_SM-LP-5001

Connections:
/Audio-Codec/HP_L: C23.1; also elsewhere on the board
/Audio-Codec/LINE_IN: C22.2; also elsewhere on the board
GND: T1.3 (SA), T2.2 (AB); also elsewhere on the board
GNDA: J2.3, R5.2, T1.2 (AB), T2.3 (SA)
unnamed: C21.1, J2.1
unnamed: C24.1, R4.2, R5.1
unnamed: C24.2, J2.2
unnamed: C21.2, T1.1 (AA)
unnamed: C22.1, T1.4 (SB)
unnamed: C23.2, T2.1 (AA)
unnamed: R4.1, T2.4 (SB)

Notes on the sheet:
Pi-Seite (GND)
Telefonseite (GNDA)
oben Aufnahme (X_OUT → Codec), unten Wiedergabe (Codec → X_IN); R4 = 0R, R5 unbestückt
RJ12 1:1 zur Audio-Buchse

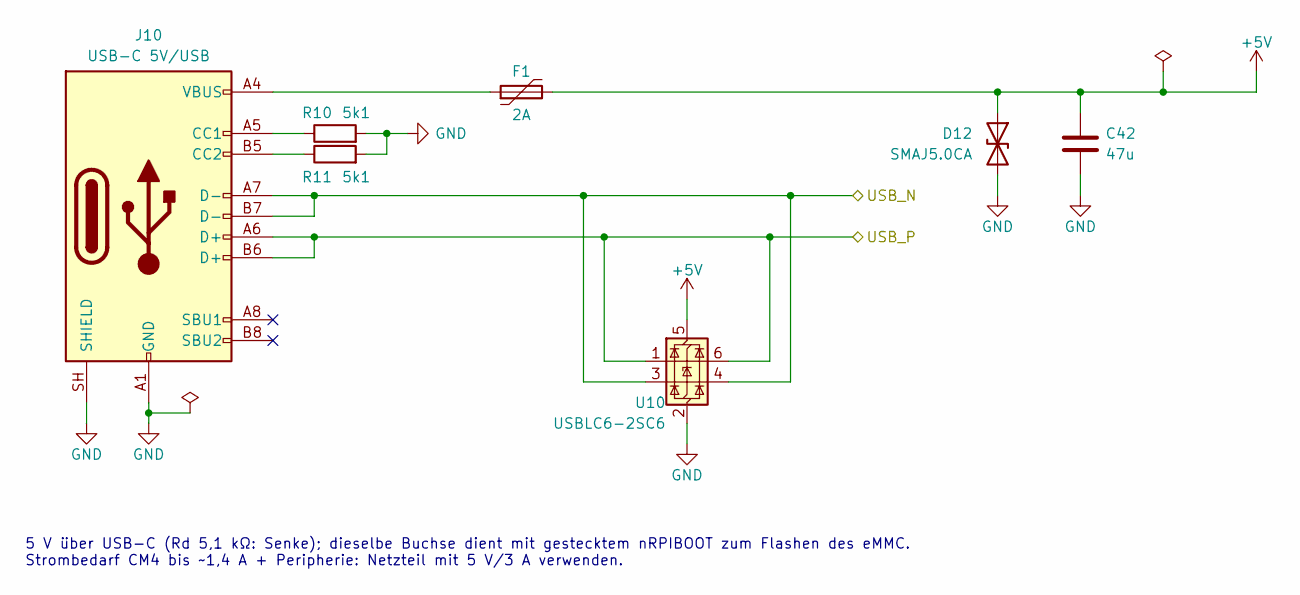
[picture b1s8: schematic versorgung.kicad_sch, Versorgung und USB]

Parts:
C42: 47u; C_1206_3216Metric
D12: SMAJ5.0CA; D_SMA
F1: 2A; Fuse_1812_4532Metric
J10: USB-C 5V/USB; USB_C_Receptacle_GCT_USB4105-xx-A_16P_TopMnt_Horizontal
R10, R11: 5k1; R_0603_1608Metric
U10: USBLC6-2SC6; SOT-23-6

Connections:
+5V: C42.1, D12.1 (A1), F1.2, U10.5 (VBUS); also elsewhere on the board
/CM4/USB_N: J10.A7 (D-), J10.B7 (D-), U10.3 (I/O2), U10.4 (I/O2); also elsewhere on the board
/CM4/USB_P: J10.A6 (D+), J10.B6 (D+), U10.1 (I/O1), U10.6 (I/O1); also elsewhere on the board
GND: C42.2, D12.2 (A2), J10.A1 (GND), J10.A12 (GND), J10.B1 (GND), J10.B12 (GND), J10.SH (SHIELD), R10.2, R11.2, U10.2 (GND); also elsewhere on the board
unnamed: F1.1, J10.A4 (VBUS), J10.A9 (VBUS), J10.B4 (VBUS), J10.B9 (VBUS)
unnamed: J10.A5 (CC1), R10.1
unnamed: J10.B5 (CC2), R11.1

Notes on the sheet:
5 V über USB-C (Rd 5,1 kΩ: Senke); dieselbe Buchse dient mit gestecktem nRPIBOOT zum Flashen des eMMC. Strombedarf CM4 bis ~1,4 A + Peripherie: Netzteil mit 5 V/3 A verwenden.

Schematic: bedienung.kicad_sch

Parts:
D1: grün; LED_0603_1608Metric
D2: gelb; LED_0603_1608Metric
D3: blau; LED_0603_1608Metric
H1, H2, H3, H4: M2.5; MountingHole_2.7mm_M2.5
R6, R7, R8: 330; R_0603_1608Metric
R9: DNP; R_0603_1608Metric; not fitted
SW1: Taste; SW_SPST_TL3342
SW2: Konfig; SW_SPST_TL3342
SW3: Ein/Aus; SW_SPST_TL3342

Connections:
+3V3: R9.1; also elsewhere on the board
/Bedienung/LED_GESPRAECH: R7.1; also elsewhere on the board
/Bedienung/LED_STATUS: R8.1; also elsewhere on the board
/Bedienung/LED_TELEFON: R6.1; also elsewhere on the board
/Bedienung/TASTE: SW1.1; also elsewhere on the board
/Bedienung/TASTE_EIN_AUS: R9.2, SW3.1; also elsewhere on the board
/Bedienung/TASTE_KONFIG: SW2.1; also elsewhere on the board
GND: D1.1 (K), D2.1 (K), D3.1 (K), SW1.2, SW2.2, SW3.2; also elsewhere on the board
unnamed: D1.2 (A), R6.2
unnamed: D2.2 (A), R7.2
unnamed: D3.2 (A), R8.2

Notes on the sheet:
D1: Telefon verbunden
D2: Gespräch
Annehmen/Auflegen
(Pull-up im Pi)
D3: Status/Konfiguration
Konfiguration (Pull-up im Pi)
H1–H4: Gehäusebefestigung M2,5 (Lage nach Gehäuse); CM4 auf 4 Abstandsbolzen M2,5
Ein/Aus (GPIO3): Druck im Betrieb = sauber herunterfahren (dtoverlay=gpio-shutdown), Druck im Halt = starten (Bootloader WAKE_ON_GPIO=1). R9 nur bestücken, falls nötig.

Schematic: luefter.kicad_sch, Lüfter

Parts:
C46: 10u; C_0805_2012Metric
D13: MBR140SFT1G; D_SOD-123F
J15: Lüfter 5 V; JST_PH_B2B-PH-K_1x02_P2.00mm_Vertical
Q11: AO3400A; SOT-23
R17: 100; R_0603_1608Metric
R18: 100k; R_0603_1608Metric

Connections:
+5V: C46.1, D13.1 (K), J15.1; also elsewhere on the board
/CM4/LUEFTER: R17.1; also elsewhere on the board
GND: C46.2, Q11.2 (S), R18.2; also elsewhere on the board
unnamed: D13.2 (A), J15.2, Q11.3 (D)
unnamed: Q11.1 (G), R17.2, R18.1

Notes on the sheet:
Steuerung über die SoC-Temperatur: dtoverlay=gpio-fan,gpiopin=12,temp=60000 (Hysterese im Treiber). GPIO12 kann auch PWM (PWM0) für Drehzahlregelung. J15 JST PH 2,0 mm: 1 = +5 V, 2 = Lüfter −

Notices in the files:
hardware/cm4/erzeuge_schaltplan.py:
SPDX-License-Identifier: GPL-3.0-or-later
